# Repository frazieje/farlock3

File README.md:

# FARLock v3 firmware

Firmware for the third generation FARLock, an open source motorised door
deadbolt. This version is a **Matter over Thread** device built on Zephyr and
the nRF Connect SDK, meant to be commissioned into Home Assistant through a
Thread border router. It replaces the v2 firmware
([farlock_nrf52](https://github.com/frazieje/farlock_nrf52)), which used
Bluetooth 6LoWPAN, MQTT and custom apps.

Hardware: <https://github.com/frazieje/farlock3-hw> (nRF52840, TB6612FNG
h-bridge, QSPI flash for DFU, USB console, NFC antenna).

## Features

- Matter Door Lock cluster with users, PIN credentials and optional schedules
  (Thread sleepy end device, ICD).
- Real bolt control: TB6612FNG motor driver, limit switch feedback, handedness
  switch, jam detection reported as a Matter `LockJammed` alarm, manual
  thumb-turn changes reported as `Manual` operations.
- NFC: the lock emulates a writable NFC Forum Type 4 Tag. Write a Home
  Assistant tag into it with the companion app, then tapping the lock with a
  phone fires `tag_scanned` in Home Assistant and an automation locks or
  unlocks through Matter.
- Matter OTA with MCUboot, secondary slot in external QSPI flash.
- USB CDC ACM console and shell in debug builds.

## Repository layout

This repository is the manifest repository of a west workspace (T2 topology).

```
farlock3/            this repo (manifest)
├── app/             the Zephyr application (derived from NCS samples/matter/lock)
├── boards/frazieje/farlock3/   custom board definition
├── dts/bindings/    devicetree bindings for the motor and switches
└── west.yml         pins nRF Connect SDK v3.3.0
```

## Building

```sh
west init -m https://github.com/frazieje/farlock3 --mr main farlock3-ws
cd farlock3-ws
west update

# debug build for the real board
west build -b farlock3 farlock3/app

# release build (no console, no USB, watchdog)
west build -b farlock3 farlock3/app -- -DFILE_SUFFIX=release

# nRF52840 DK bench build (motor on P0.28..P0.31, switches on buttons 3/4)
west build -b nrf52840dk/nrf52840 farlock3/app

# flash
west flash
```

With the toolchain installed by `nrfutil sdk-manager`, prefix the build with
`nrfutil toolchain-manager launch --ncs-version v3.3.0 --`.

Useful options (`-DCONFIG_...=y` or in a `.conf`):

| Option | Purpose |
|---|---|
| `FARLOCK3_LOCK_SIMULATED` | No motor or switches, actions complete after a delay |
| `FARLOCK3_MOTOR_TIMEOUT_MS` | Max motor run before a jam is reported (default 3000) |
| `FARLOCK3_MOTOR_DUTY_CYCLE` | Motor PWM duty in percent (default 100) |
| `LOCK_SCHEDULES` | Week day, year day and holiday schedules (`-DEXTRA_CONF_FILE=schedules.conf`) |

## Bench testing

Debug builds expose a `farlock` shell command on the USB console
(`/dev/serial/by-id/usb-frazieje_FARLock_v3_*`, 115200 8N1):

```
farlock status   # bolt state, switch inputs, motor state
farlock lock     # drive the bolt to the locked position
farlock unlock   # drive the bolt to the unlocked position
farlock toggle
```

On the nRF52840 DK, button 2 toggles the bolt, button 3 is the handedness
switch and button 4 is the position switch. Resetting the board re-enumerates
the USB console, so reopen the terminal after a reset or factory reset.

To check the external QSPI flash, wake it first: the application puts it
into deep power-down at boot, and the flash shell panics on a suspended
device.

```
pm resume mx25r6435f@0
flash read mx25r6435f@0 0 32
flash erase mx25r6435f@0 0x7F0000 0x1000
flash write mx25r6435f@0 0x7F0000 0xDEADBEEF 0x01234567
flash read mx25r6435f@0 0x7F0000 16
flash erase mx25r6435f@0 0x7F0000 0x1000
pm suspend mx25r6435f@0
```

The flash shell parses sizes as hexadecimal, so erase sizes must be written
as `0x1000`, not `4096`. The last sector (0x7F0000) is outside every
partition. Keep shell lines under about 60 characters; the USB console drops
input beyond its receive buffer.

## Firmware update

Once the board carries this partition map (MCUboot 64 KB at 0x0, application
slot at 0x10000), it never needs the SWD header again. Three update paths
exist; all of them take the signed application image that every build
produces (`build-*/app/zephyr/zephyr.signed.hex`, or the Matter OTA file
`build-*/dfu_application.zip`).

### USB serial recovery (MCUboot)

MCUboot enumerates as `1915:0005 FARLock v3 bootloader` and keeps the
connection LED lit while in recovery mode. It enters recovery when:

- the program button (P0.12, J6 pin 3) is held while power is applied,
- the running application asks for it (`farlock dfu` on the debug console),
- there is no bootable application in the primary slot.

Upload with any MCUmgr client. `smpmgr` (pip) is known to work; nrfutil does
not recognise this bootloader because it identifies MCUboot devices by a
fixed VID:PID list. One-time setup in the west workspace root:

```
python3 -m venv .venv-smp && .venv-smp/bin/pip install smpmgr
```

Then, with the board in recovery mode:

```
P=/dev/serial/by-id/usb-frazieje_FARLock_v3_bootloader_*-if00
.venv-smp/bin/smpmgr --port $P --line-buffers 8 image state-read
.venv-smp/bin/smpmgr --port $P --line-buffers 8 image upload \
    build-farlock3/app/zephyr/zephyr.signed.bin
.venv-smp/bin/smpmgr --port $P os reset
```

`--line-buffers 8` matches MCUboot's receive buffering and makes the upload
about twice as fast (roughly one minute for a debug image). The upload goes
straight into the primary slot, so it does not depend on the external flash;
the bootloader refuses to erase that slot, and a half-finished upload simply
leaves the device in recovery mode (no bootable image) for another attempt.

### Bluetooth LE (nRF Connect Device Manager)

A short press of the program button starts the SMP update service over
Bluetooth LE for as long as the connection lasts. Before commissioning it is
started together with the Matter commissioning advertisement; afterwards the
press starts only the update service. Open the nRF Connect Device Manager
app (Android or iOS), connect to `FARLock3`, upload `zephyr.signed.bin` from
`dfu_application.zip` and choose test-and-confirm. The image lands in the
QSPI secondary slot, MCUboot swaps it in on the following reboot, and the
application confirms it after a successful start, so a broken image reverts
by itself. There is no authentication on the SMP service; the physical
button press is the access control.

The same works from a Linux host with a Bluetooth adapter, using the smpmgr
client from the section above (the lock advertises as `FARLock3`; its random
address changes, so scan first):

```
.venv-smp/bin/smpmgr --ble <address> image upload build-farlock3/app/zephyr/zephyr.signed.bin
.venv-smp/bin/smpmgr --ble <address> image state-write <hash of the new image>
.venv-smp/bin/smpmgr --ble <address> os reset
```

The image version (`CONFIG_MCUBOOT_IMGTOOL_SIGN_VERSION`) and the Matter
software version in `prj.conf` / `prj_release.conf` must be bumped for every
release: MCUmgr refuses to schedule a swap to an image identical to the
running one, and Matter OTA only accepts a higher software version.

### Matter OTA

The build also produces the Matter OTA image (`build-*/matter.ota`) for an
OTA provider on the fabric. This path needs the device commissioned on
Thread first.

## LEDs

The lock runs on a battery, so no LED is lit in steady state. Every pattern
is started by an event and ends by itself (`app/src/indication.h`):

| Event | LED | Pattern |
|---|---|---|
| Locked (motor, thumb-turn or key) | green | one 1 s flash |
| Unlocked | red | one 1 s flash |
| Motor running | target colour | fast blink until the bolt arrives |
| Jam | red and green | alternate five times |
| NFC tag read by a phone | green | one short flash |
| Commissioning advertising (after a button tap) | connection | short blink once a second, 15 min in release builds |
| Phone connected over Bluetooth LE | connection | fast blink |
| Joined Thread (also at every boot once commissioned) | connection | three quick flashes |
| Button tap on a commissioned lock | connection | one flash if on Thread, three if not |
| Factory reset armed (button held 3 s) | all | 500 ms blink; release to cancel, hold 3 s more to reset |
| Matter Identify | green | blink for the identify time |

## Commissioning

The device uses the Matter test vendor ID and the example lock product ID
(0x8006) with test attestation data generated at build time. Home Assistant's
Matter server accepts test devices. The QR code and manual pairing code are
printed on the console at boot (`factory_data.png` in the build directory
has the QR code). A short press of the program button starts the
commissioning advertisement; hold it for more than 3 s to factory reset.

### Radio range

The lock transmits at +8 dBm, the nRF52840 maximum (`OPENTHREAD_DEFAULT_TX_POWER`
in `app/Kconfig`). A steel door and a couple of walls cost 20-30 dB, so check
the link from the border router after installation:

```
ot-ctl neighbor linkquality
```

An average RSS better than -75 dBm and a frame error rate under 5 % is a solid
link. If the border router's own radio is at 0 dBm (`ot-ctl txpower`), raising
it to 8 helps the direction that column measures. Thread channels 15, 20, 25
sit between the Wi-Fi channels 1/6/11; channel 25 is the usual choice when all
three Wi-Fi channels are in use nearby. Beyond that, a mains-powered Thread
router between the border router and the door turns one long hop into two
short ones.

## Licence

Application sources derived from the nRF Connect SDK keep their
`LicenseRef-Nordic-5-Clause` headers; new files are Apache-2.0.

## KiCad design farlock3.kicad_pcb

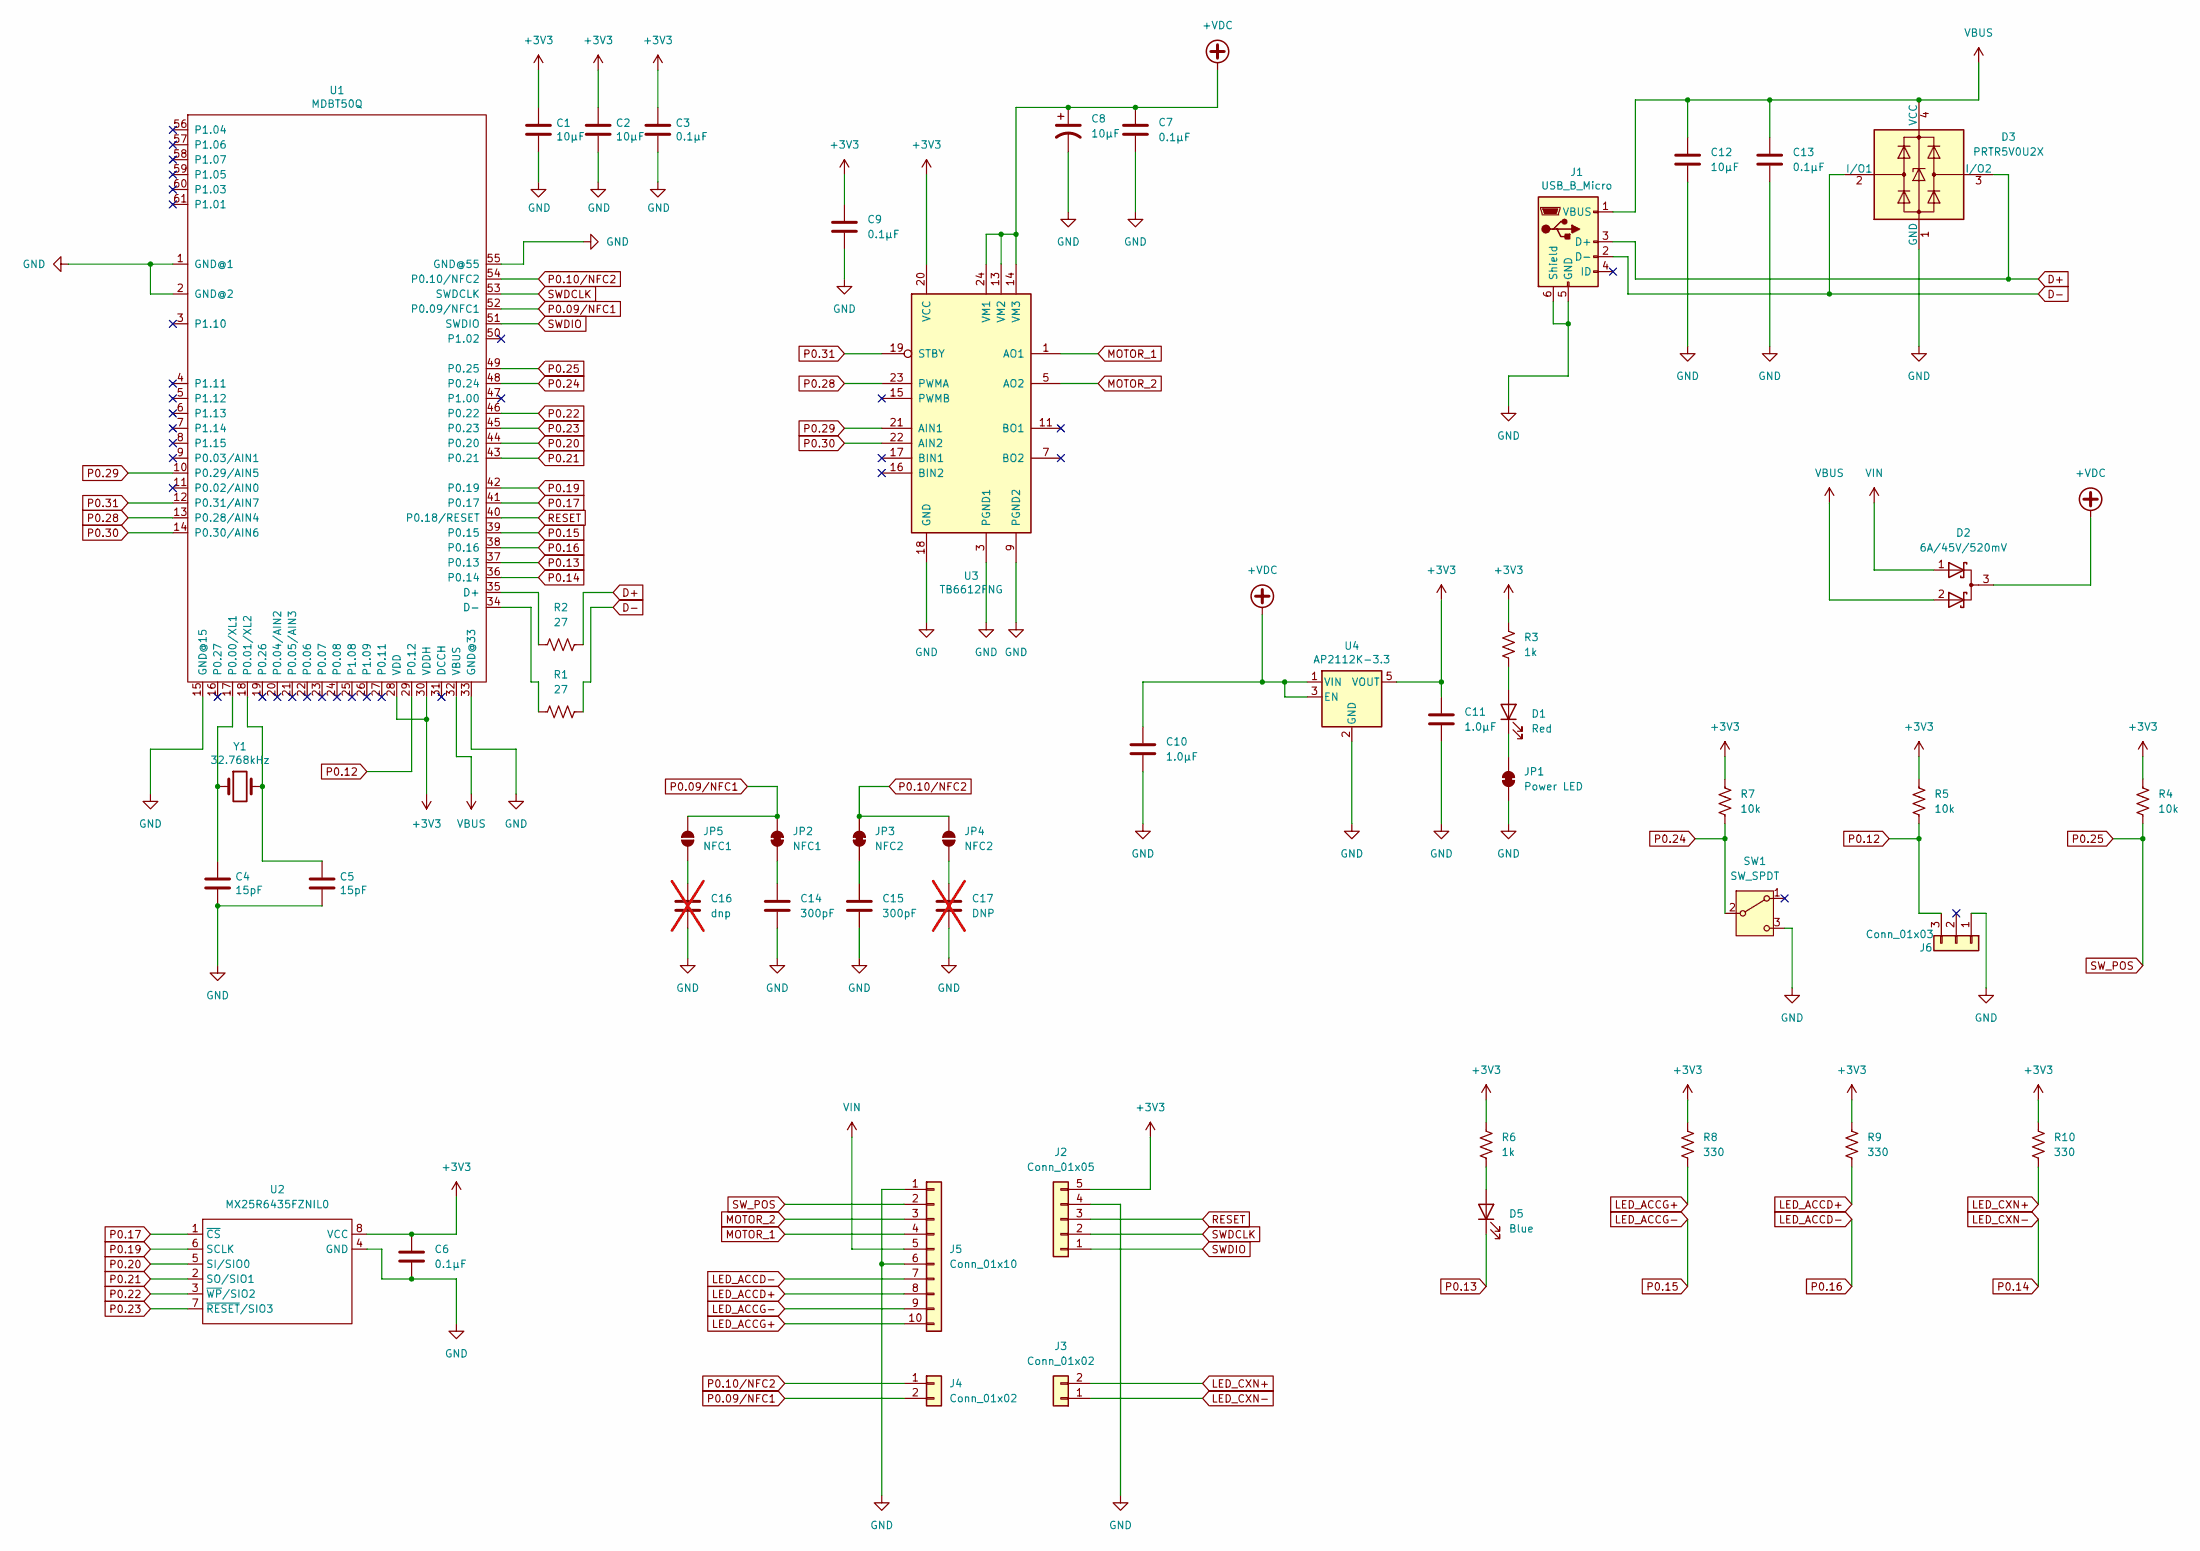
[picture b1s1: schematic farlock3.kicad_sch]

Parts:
C1, C2, C12: 10µF; C_0603_1608Metric; Manufacturer Part No CL10A106MP8NNNC
C3, C6, C7, C9, C13: 0.1µF; C_0603_1608Metric; Manufacturer Part No CL10B104KA8NNNC
C4, C5: 15pF; C_0603_1608Metric; Manufacturer Part No CL10C150JB8NNNC
C8: 10µF; CP_EIA-3528-21_Kemet-B; Manufacturer Part No 593D106X9020B2TE3
C10, C11: 1.0µF; C_0603_1608Metric; Manufacturer Part No CL10A105KO8NNNC
C14, C15: 300pF; C_0603_1608Metric; Manufacturer Part No C0603C301F5HACTU
C16: dnp; C_0603_1608Metric; not fitted
C17: DNP; C_0603_1608Metric; not fitted
D1: Red; LED_0603_1608Metric; Manufacturer Part No LTST-C190KRKT
D2: 6A/45V/520mV; TO-277A; Manufacturer Part No V10PL45-M3/86A
D3: PRTR5V0U2X; SOT-143; Manufacturer Part No PRTR5V0U2X
D5: Blue; LED_0603_1608Metric; Manufacturer Part No KB EELP41.12-P1R2-36-3X4X-5-R18
J1: USB_B_Micro; USB_Micro-B_Amphenol_10104110_Horizontal; Manufacturer Part No 10104110-0001LF
J2: Conn_01x05; PinHeader_1x05_P2.54mm_Vertical
J3, J4: Conn_01x02; PinHeader_1x02_P2.54mm_Vertical
J5: Conn_01x10; PinHeader_1x10_P2.54mm_Vertical
J6: Conn_01x03; PinHeader_1x03_P2.54mm_Vertical
JP1: Power LED; SolderJumper-2_P1.3mm_Bridged_RoundedPad1.0x1.5mm
JP2: NFC1; SolderJumper-2_P1.3mm_Bridged_RoundedPad1.0x1.5mm
JP3: NFC2; SolderJumper-2_P1.3mm_Bridged_RoundedPad1.0x1.5mm
JP4: NFC2; SolderJumper-2_P1.3mm_Open_RoundedPad1.0x1.5mm
JP5: NFC1; SolderJumper-2_P1.3mm_Open_RoundedPad1.0x1.5mm
R1, R2: 27; R_0603_1608Metric; Manufacturer Part No ERA-3AHD270V
R3, R6: 1k; R_0603_1608Metric; Manufacturer Part No ERA-3AEB102V
R4, R5, R7: 10k; R_0603_1608Metric; Manufacturer Part No ERJ-3GEYJ103V
R8, R9, R10: 330; R_0603_1608Metric; Manufacturer Part No ERA-3AEB331V
SW1: SW_SPDT; OS102011MA1QN1; Manufacturer Part No OS102011MA1QN1
U1: MDBT50Q; MDBT50Q-U1M; Manufacturer Part No MDBT50Q-U1MV2
U2: MX25R6435FZNIL0; WSON-8-1EP_6x5mm_P1.27mm_EP3.4x4mm; Manufacturer Part No MX25R6435FZNIL0
U3: TB6612FNG; SSOP-24_5.3x8.2mm_P0.65mm; Manufacturer Part No TB6612FNG,C,8,EL
U4: AP2112K-3.3; SOT-23-5; Manufacturer Part No AP2112K-3.3TRG1
Y1: 32.768kHz; Crystal_SMD_3215-2Pin_3.2x1.5mm; Manufacturer Part No CM7V-T1A-LOW-ESR-32.768KHZ-9PF-20-TA-QC

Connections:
+3V3: C1.1, C2.1, C3.1, C6.1, C9.1, C11.1, J2.5, R3.1, R4.2, R5.2, R6.1, R7.2, R8.1, R9.1, R10.1, U1.28 (VDD), U1.30 (VDDH), U2.8 (VCC), U3.20 (VCC), U4.5 (VOUT)
+VDC: C7.1, C8.1, C10.1, D2.3 (K), U3.13 (VM2), U3.14 (VM3), U3.24 (VM1), U4.1 (VIN), U4.3 (EN)
D+: D3.3 (I/O2), J1.3 (D+), R2.2
D-: D3.2 (I/O1), J1.2 (D-), R1.2
GND: C1.2, C2.2, C3.2, C4.2, C5.2, C6.2, C7.2, C8.2, C9.2, C10.2, C11.2, C12.2, C13.2, C14.2, C15.2, C16.2, C17.2, D3.1 (GND), J1.5 (GND), J1.6 (Shield), J2.4, J5.1, J5.6, J6.1, JP1.1 (A), SW1.3 (C), U1.1 (GND@1), U1.2 (GND@2), U1.15 (GND@15), U1.33 (GND@33), U1.55 (GND@55), U2.4 (GND), U3.3 (PGND1), U3.4 (PGND1), U3.9 (PGND2), U3.10 (PGND2), U3.18 (GND), U4.2 (GND)
LED_ACCD+: J5.8, R9.2
LED_ACCD-: J5.7, U1.38 (P0.16)
LED_ACCG+: J5.10, R8.2
LED_ACCG-: J5.9, U1.39 (P0.15)
LED_CXN+: J3.2, R10.2
LED_CXN-: J3.1, U1.36 (P0.14)
MOTOR_1: J5.4, U3.1 (AO1), U3.2 (AO1)
MOTOR_2: J5.3, U3.5 (AO2), U3.6 (AO2)
unnamed: D1.2 (A), R3.2
unnamed: D1.1 (K), JP1.2 (B)
unnamed: D5.2 (A), R6.2
unnamed: C14.1, JP2.1 (A)
unnamed: C15.1, JP3.1 (A)
unnamed: C17.1, JP4.1 (A)
unnamed: C16.1, JP5.1 (A)
unnamed: R2.1, U1.35 (D+)
unnamed: R1.1, U1.34 (D-)
unnamed: C4.1, U1.17 (P0.00/XL1), Y1.1
unnamed: C5.1, U1.18 (P0.01/XL2), Y1.2
P0.09/NFC1: J4.2, JP2.2 (B), JP5.2 (B), U1.52 (P0.09/NFC1)
P0.10/NFC2: J4.1, JP3.2 (B), JP4.2 (B), U1.54 (P0.10/NFC2)
P0.12: J6.3, R5.1, U1.29 (P0.12)
P0.13: D5.1 (K), U1.37 (P0.13)
P0.17: U1.41 (P0.17), U2.1 (~CS)
P0.19: U1.42 (P0.19), U2.6 (SCLK)
P0.20: U1.44 (P0.20), U2.5 (SI/SIO0)
P0.21: U1.43 (P0.21), U2.2 (SO/SIO1)
P0.22: U1.46 (P0.22), U2.3 (~WP/SIO2)
P0.23: U1.45 (P0.23), U2.7 (~RESET/SIO3)
P0.24: R7.1, SW1.2 (B), U1.48 (P0.24)
P0.25: J5.2, R4.1, U1.49 (P0.25)
P0.28: U1.13 (P0.28/AIN4), U3.23 (PWMA)
P0.29: U1.10 (P0.29/AIN5), U3.21 (AIN1)
P0.30: U1.14 (P0.30/AIN6), U3.22 (AIN2)
P0.31: U1.12 (P0.31/AIN7), U3.19 (STBY)
RESET: J2.3, U1.40 (P0.18/RESET)
SWDCLK: J2.2, U1.53 (SWDCLK)
SWDIO: J2.1, U1.51 (SWDIO)
VBUS: C12.1, C13.1, D2.2 (A), D3.4 (VCC), J1.1 (VBUS), U1.32 (VBUS)
VIN: D2.1 (A), J5.5

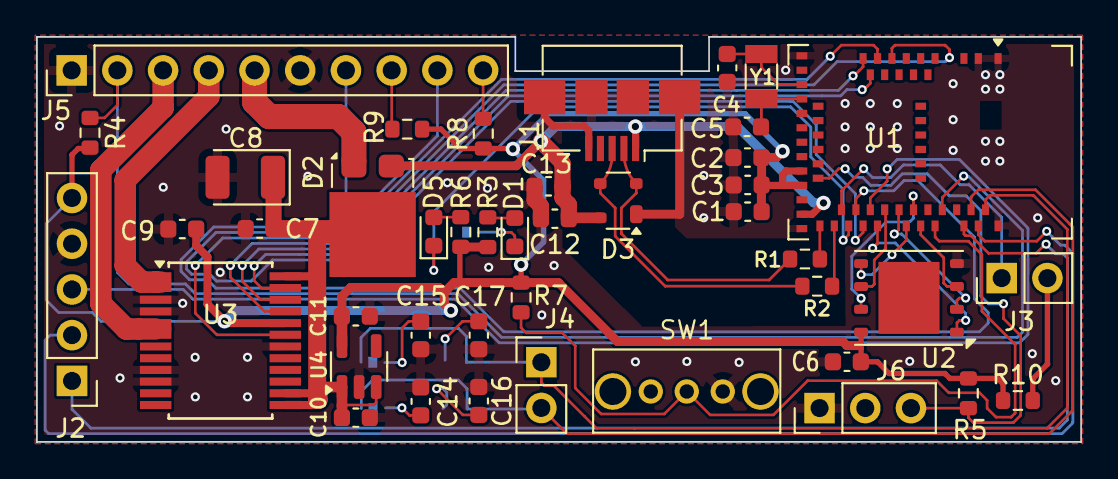
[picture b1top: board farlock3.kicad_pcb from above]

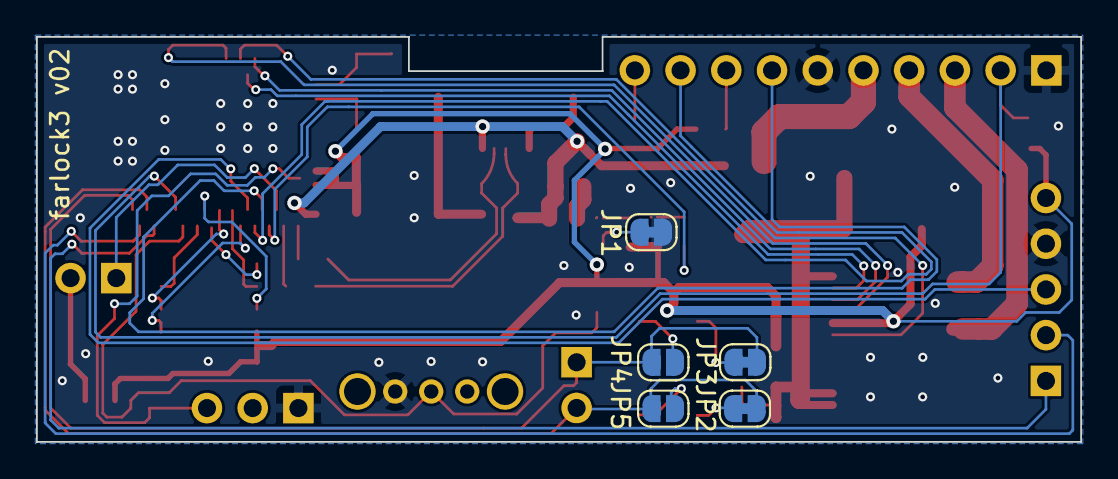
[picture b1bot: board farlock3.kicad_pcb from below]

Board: 2 copper layers, 58.0 x 22.5 mm, 48 parts (5 on the bottom side), 45 nets.

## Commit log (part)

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2025-05-29 add MDBT50Q library
2025-05-29 use new kicad formats, add MDBT50Q lib
2025-06-14 farlock3 v01 layout, production files
2025-06-19 v02 redesign
2025-06-19 add schematic PDF and board render
2025-06-23 increase minimum track width, spacing, and annular ring size - support more board fabrication houses
2026-05-09 Initial commit for farlock3
2026-05-13 add workspace and module
2026-05-13 add board definition
2026-05-13 refactor configs and dts. working build
2026-05-13 reorganize into an app/ topology. remove unused overlays and confs
2026-05-15 usb wip
2026-05-19 wip ndef storage
